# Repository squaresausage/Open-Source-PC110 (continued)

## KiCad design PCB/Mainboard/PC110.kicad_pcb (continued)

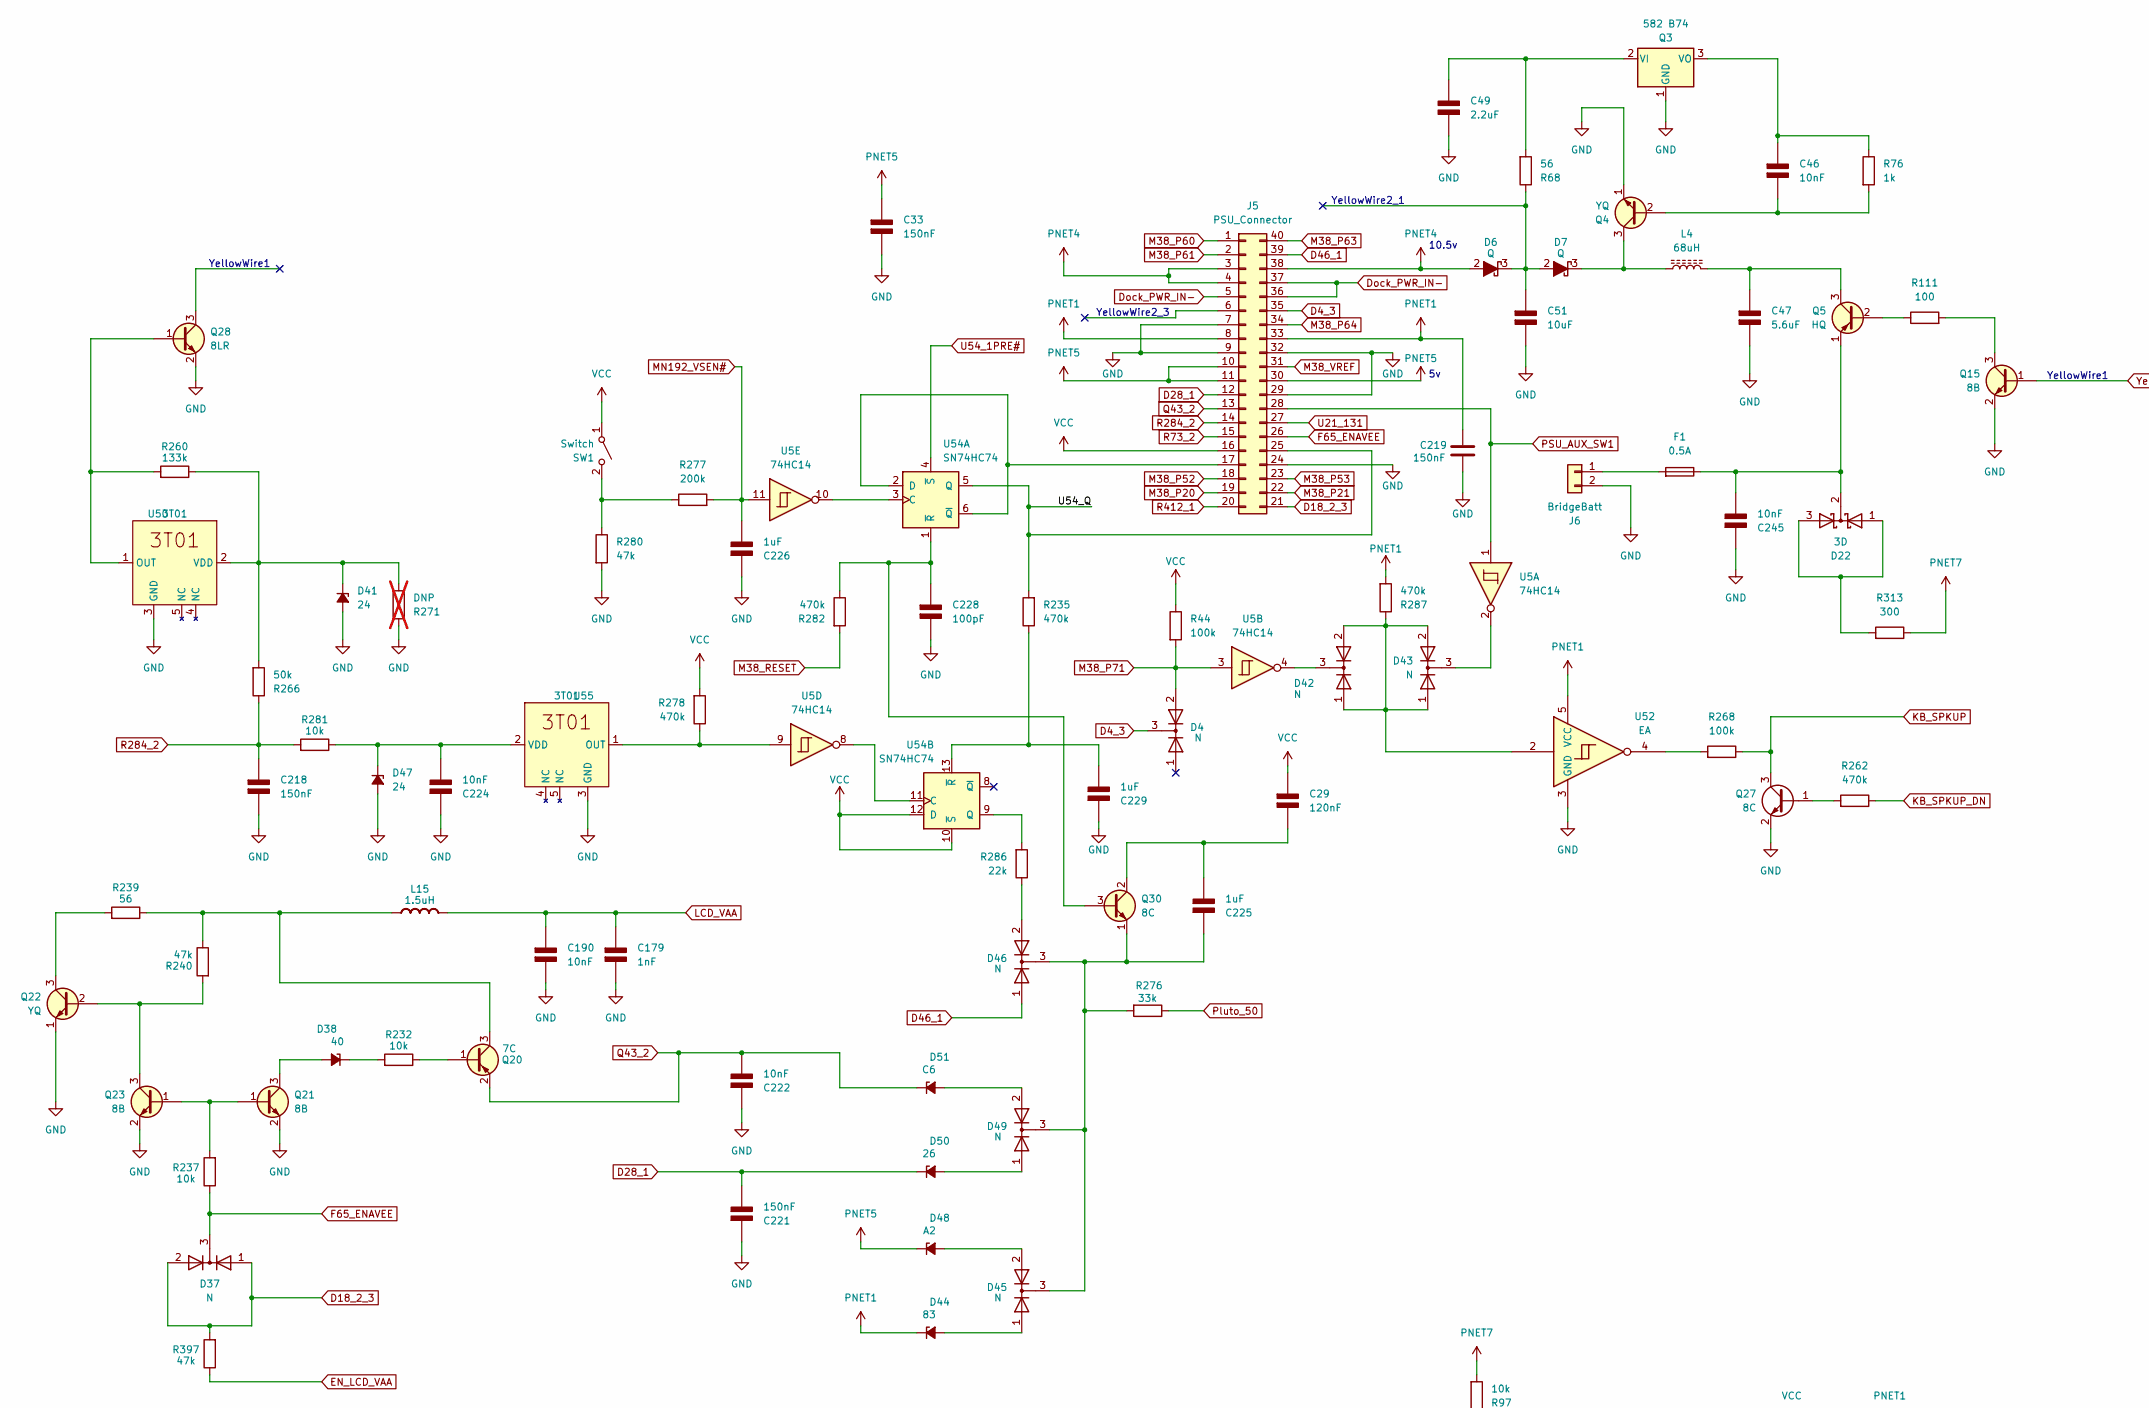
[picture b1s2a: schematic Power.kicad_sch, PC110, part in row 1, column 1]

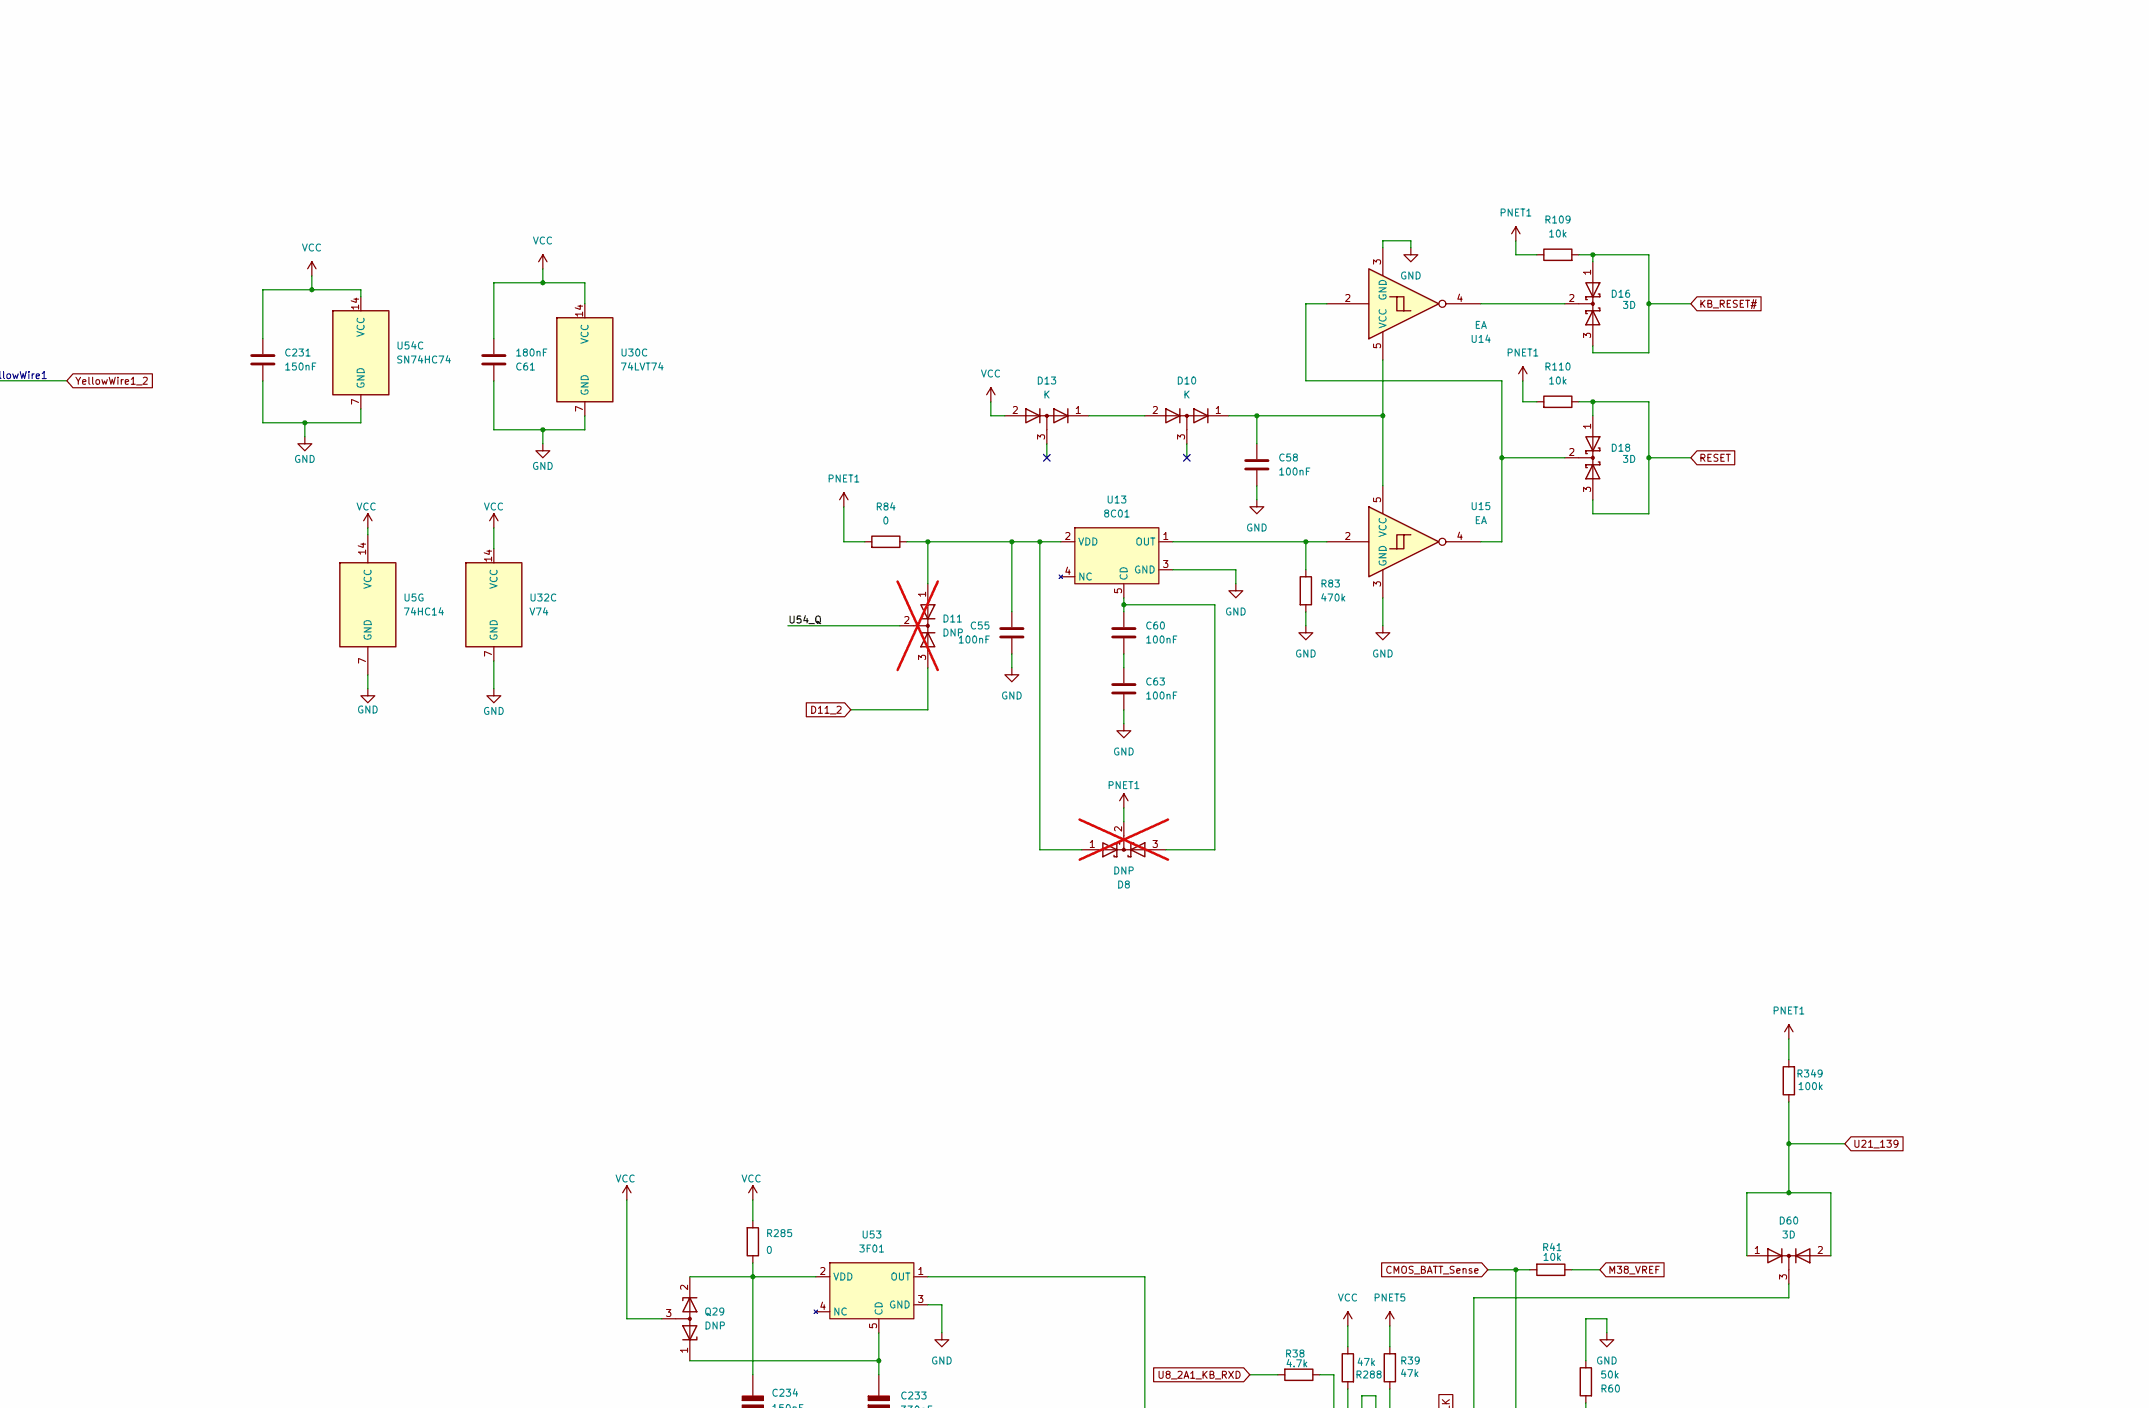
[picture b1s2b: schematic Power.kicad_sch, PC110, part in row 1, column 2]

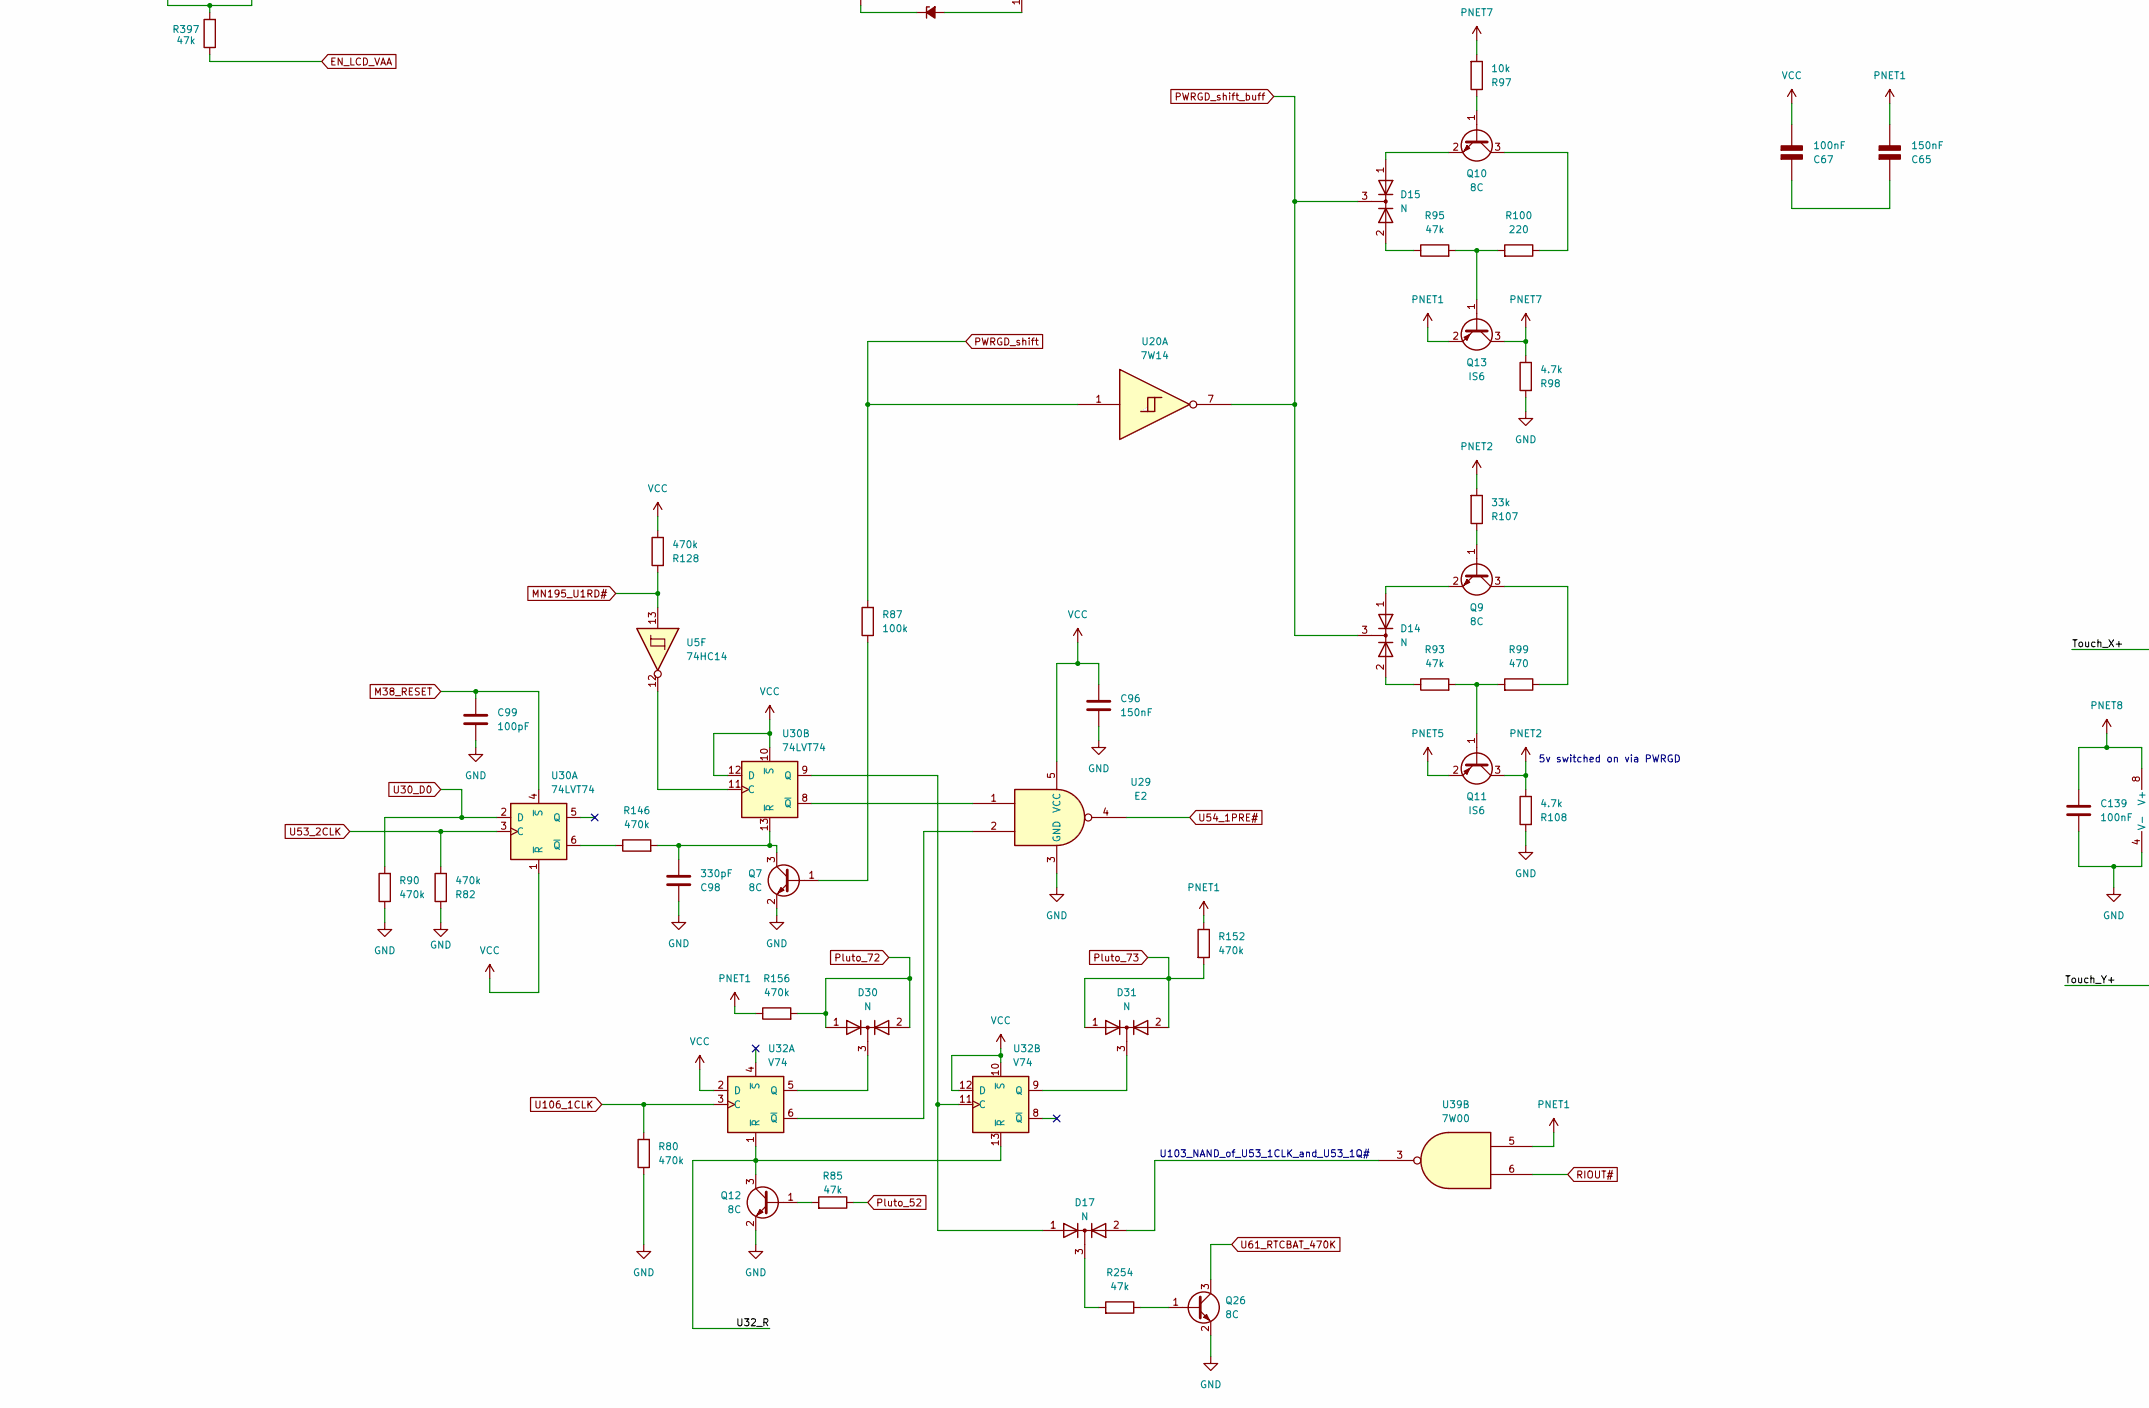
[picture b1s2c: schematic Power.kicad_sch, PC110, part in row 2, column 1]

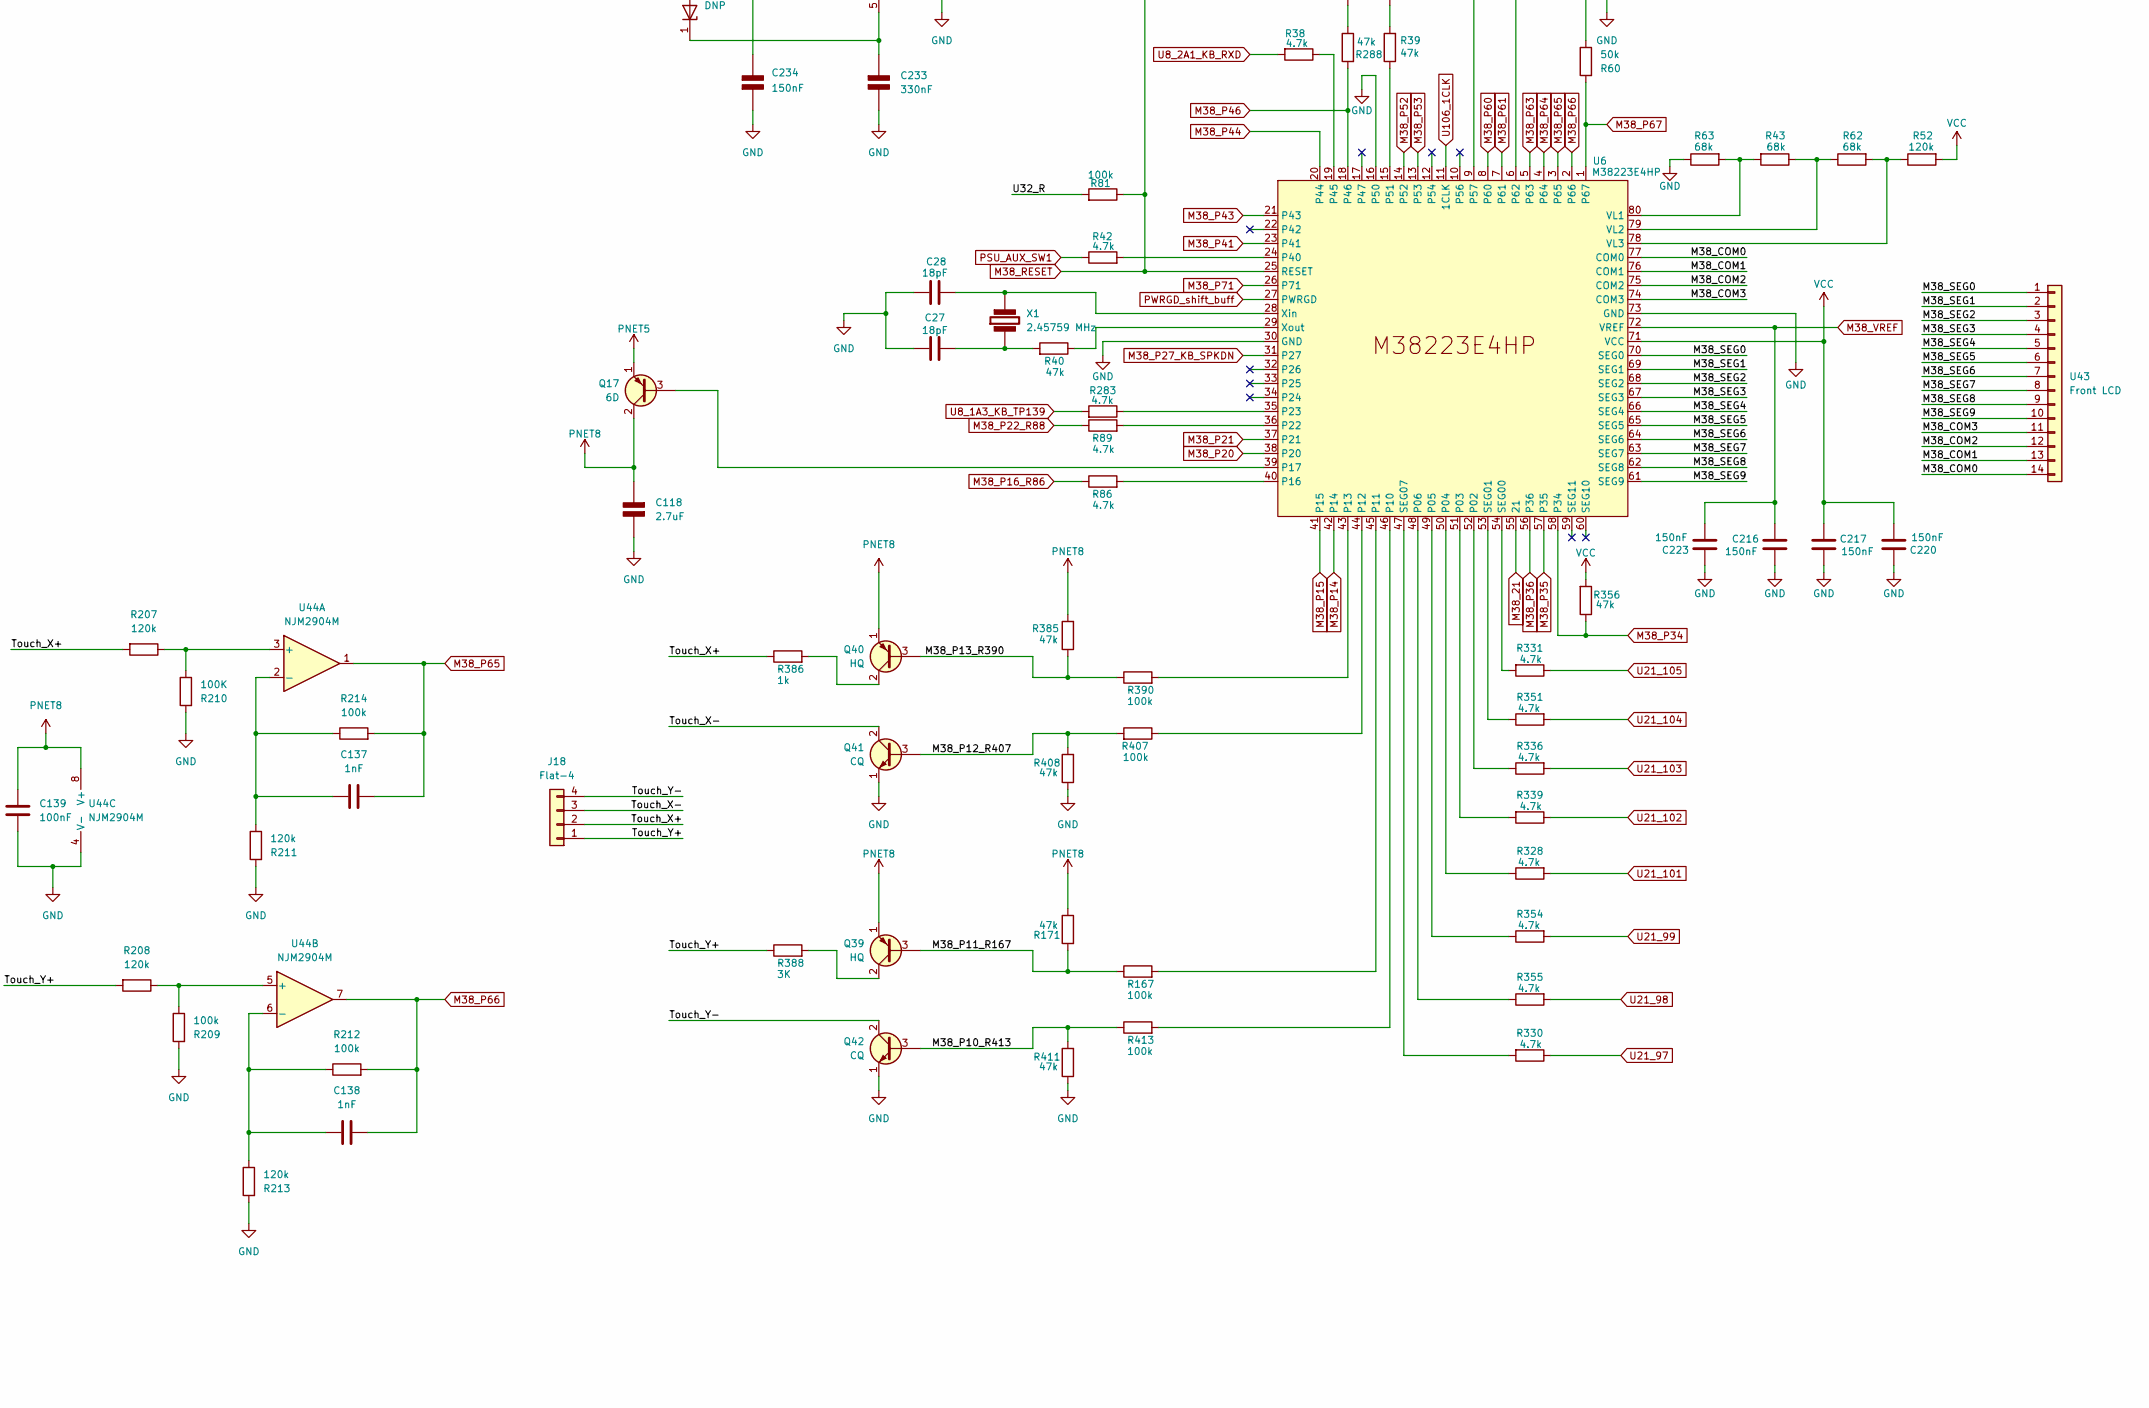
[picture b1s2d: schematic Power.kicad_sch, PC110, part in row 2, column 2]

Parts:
C27, C28: 18pF; C_0402_1005Metric
C29: 120nF; C_0402_1005Metric
C33, C65, C96, C216, C217, C219, C220, C223, C231, C234: 150nF; C_0402_1005Metric
C46, C190, C222, C224, C245: 10nF; C_0603_1608Metric
C47: 5.6uF; C_1206_3216Metric
C49: 2.2uF; C_0805_2012Metric
C51: 10uF; C_1206_3216Metric
C55, C58, C67, C139: 100nF; C_0402_1005Metric
C60, C63: 100nF; C_0603_1608Metric
C61: 180nF; C_0402_1005Metric
C98: 330pF; C_0402_1005Metric
C99, C228: 100pF; C_0402_1005Metric
C118: 2.7uF; C_0805_2012Metric
C137, C138, C179: 1nF; C_0402_1005Metric
C218, C221: 150nF; C_0603_1608Metric
C225, C226, C229: 1uF; C_0603_1608Metric
C233: 330nF; C_0603_1608Metric
D4, D14, D15, D17, D30, D31, D37, D42, D43, D45, D46, D49: N; SOT-416L
D6, D7: Q; 3D
D8, D11: DNP; 3D; not fitted
D10, D13: K; SOT-416L
D16, D18, D22: 3D
D38: 40; D_0603_1608Metric
D41, D47: 24; D_0603_1608Metric
D44: 83; D_0603_1608Metric
D48: A2; D_0603_1608Metric
D50: 26; D_0603_1608Metric
D51: C6; D_0603_1608Metric
D60: 3D; SOT-23
F1: 0.5A; Fuse_1206_3216Metric
J5: PSU_Connector
J6: BridgeBatt
J18: Flat-4
L4: 68uH; L_1210_3225Metric
L15: 1.5uH; L_0603_1608Metric
Q3: 582 B74; SOT-89-3
Q4, Q22: YQ; SOT-416L
Q5: HQ; SOT-416L
Q7, Q10, Q12, Q26, Q27, Q30: 8C; SOT-416
Q9: 8C; SOT-523
Q11, Q13: IS6; SOT-23
Q15, Q21, Q23: 8B; SOT-416
Q17: 6D; 3D
Q20: 7C; TSOT-23
Q28: 8LR; SOT-416
Q29: DNP; SOT-23
Q39, Q40: HQ; TSOT-23
Q41, Q42: CQ; TSOT-23
R38, R42, R86, R89, R98, R108, R283, R328, R330, R331, R336, R339, R351, R354, R355: 4.7k; R_0402_1005Metric
R39, R40, R85, R93, R95, R171, R240, R254, R280, R288, R356, R385, R397, R408, R411: 47k; R_0402_1005Metric
R41, R97, R109, R110, R232, R237, R281: 10k; R_0402_1005Metric
R43, R62, R63: 68k; R_0402_1005Metric
R44, R81, R87, R167, R209, R212, R214, R268, R349, R390, R407, R413: 100k; R_0402_1005Metric
R52, R207, R208, R211, R213: 120k; R_0402_1005Metric
R60, R266: 50k; R_0402_1005Metric
R68: 56; R_0805_2012Metric
R76, R386: 1k; R_0402_1005Metric
R80, R82, R83, R90, R128, R146, R152, R156, R235, R262, R278, R282, R287: 470k; R_0402_1005Metric
R84, R285: 0; R_0402_1005Metric
R99: 470; R_0402_1005Metric
R100: 220; R_0402_1005Metric
R107, R276: 33k; R_0402_1005Metric
R111: 100; R_0603_1608Metric
R210: 100K; R_0402_1005Metric
R239: 56; R_0603_1608Metric
R260: 133k; R_0402_1005Metric
R271: DNP; R_0402_1005Metric; not fitted
R277: 200k; R_0402_1005Metric
R286: 22k; R_0402_1005Metric
R313: 300; R_0805_2012Metric
R388: 3K; R_0402_1005Metric
SW1: Switch
U5: 74HC14; TSSOP-14_4.4x5mm_P0.65mm
U6: M38223E4HP; QFN-80
U13: 8C01; SOT-23-5
U14, U15, U52: EA; SOT-353
U20: 7W14; sso-8
U29: E2; SOT-353
U30: 74LVT74; TSSOP-14_4.4x5mm_P0.65mm
U32: V74; TSSOP-14_4.4x5mm_P0.65mm
U39: 7W00; sso-8
U43: Front LCD; LCD
U44: NJM2904M; soic-8-small
U50: 3T01; SOT-23-5
U53: 3F01; TSOP-5_1.65x3.05mm_P0.95mm
U54: SN74HC74; TSSOP-14_4.4x5mm_P0.65mm
U55: 3T01; TSOP-5_1.65x3.05mm_P0.95mm
X1: 2.45759 MHz; XTAL-2

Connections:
/Power/M38_COM0: U6.77 (COM0), U43.14
/Power/M38_COM1: U6.76 (COM1), U43.13
/Power/M38_COM2: U6.75 (COM2), U43.12
/Power/M38_COM3: U6.74 (COM3), U43.11
/Power/M38_P10_R413: Q42.3 (B), R411.2, R413.1
/Power/M38_P11_R167: Q39.3 (B), R167.1, R171.2
/Power/M38_P12_R407: Q41.3 (B), R407.2, R408.2
/Power/M38_P13_R390: Q40.3 (B), R385.1, R390.1
/Power/M38_SEG0: U6.70 (SEG0), U43.1
/Power/M38_SEG1: U6.69 (SEG1), U43.2
/Power/M38_SEG2: U6.68 (SEG2), U43.3
/Power/M38_SEG3: U6.67 (SEG3), U43.4
/Power/M38_SEG4: U6.66 (SEG4), U43.5
/Power/M38_SEG5: U6.65 (SEG5), U43.6
/Power/M38_SEG6: U6.64 (SEG6), U43.7
/Power/M38_SEG7: U6.63 (SEG7), U43.8
/Power/M38_SEG8: U6.62 (SEG8), U43.9
/Power/M38_SEG9: U6.61 (SEG9), U43.10
/Power/Touch_X+: J18.2, R207.2, R386.1
/Power/Touch_X-: J18.3, Q41.2 (C)
/Power/Touch_Y+: J18.1, R208.2, R388.1
/Power/Touch_Y-: J18.4, Q42.2 (C)
/Power/U32_R: Q12.3 (C), R81.2, U32.1 (~R), U32.13 (~R)
/Power/U54_Q: D11.2 (K), J5.25, R235.2, U54.5 (Q)
CMOS_BATT_Sense: R41.2, U6.6 (P62); also elsewhere on the board
D4_3: D4.3, J5.35
D18_2_3: D37.1, D37.2, J5.21, R397.2
D28_1: C221.2 (-), D50.1 (K), J5.12; also elsewhere on the board
D46_1: D46.1, J5.39
Dock_PWR_IN-: J5.5, J5.36, J5.37; also elsewhere on the board
EN_LCD_VAA: R397.1; also elsewhere on the board
F65_ENAVEE: D37.3, J5.26, R237.1; also elsewhere on the board
KB_RESET#: D16.1 (A), D16.3 (A), R109.2; also elsewhere on the board
KB_SPKUP: Q27.3 (C), R268.1; also elsewhere on the board
KB_SPKUP_DN: R262.1; also elsewhere on the board
LCD_VAA: C179.1 (+), C190.1 (+), L15.1 (+); also elsewhere on the board
M38_21: U6.55 (21); also elsewhere on the board
M38_P14: U6.42 (P14); also elsewhere on the board
M38_P15: U6.41 (P15); also elsewhere on the board
M38_P16_R86: R86.1; also elsewhere on the board
M38_P20: J5.19, U6.38 (P20)
M38_P21: J5.22, U6.37 (P21)
M38_P22_R88: R89.1; also elsewhere on the board
M38_P27_KB_SPKDN: U6.31 (P27); also elsewhere on the board
M38_P34: R356.1, U6.58 (P34); also elsewhere on the board
M38_P35: U6.57 (P35); also elsewhere on the board
M38_P36: U6.56 (P36); also elsewhere on the board
M38_P41: U6.23 (P41); also elsewhere on the board
M38_P43: U6.21 (P43); also elsewhere on the board
M38_P44: U6.20 (P44); also elsewhere on the board
M38_P46: R288.2, U6.18 (P46); also elsewhere on the board
M38_P52: J5.18, U6.14 (P52)
M38_P53: J5.23, U6.13 (P53)
M38_P60: J5.1, U6.8 (P60)
M38_P61: J5.2, U6.7 (P61)
M38_P63: J5.40, U6.5 (P63)
M38_P64: J5.34, U6.4 (P64)
M38_P65: C137.2, R214.2, U6.3 (P65), U44.1
M38_P66: C138.2, R212.2, U6.2 (P66), U44.7
M38_P67: R60.2, U6.1 (P67); also elsewhere on the board
M38_P71: D4.2, R44.2, U5.3, U6.26 (P71)
M38_RESET: C99.2, R81.1, R282.2, U6.25 (RESET), U30.4 (~S), U53.1 (OUT)
M38_VREF: C216.1, C223.2, J5.31, R41.1, U6.72 (VREF)
MN192_VSEN#: C226.2 (-), R277.2, U5.11; also elsewhere on the board
MN195_U1RD#: R128.2, U5.13; also elsewhere on the board
unnamed: C46.1 (+), Q3.3 (VO), R76.1
unnamed: C46.2 (-), Q4.2 (B), R76.2
unnamed: C47.1 (+), L4.1, Q5.3 (C)
unnamed: C49.2 (-), Q3.2 (VI), R68.2
unnamed: C60.1, C63.2
unnamed: C65.1 (+), C67.1 (+)
unnamed: C224.2 (-), D47.1 (K), R281.1, U55.2 (VDD)
unnamed: C225.1 (+), D45.3, D46.3, D49.3, Q30.1 (E), R276.2
unnamed: C29.2 (-), C225.2 (-), Q30.2 (C)
unnamed: C228.1 (+), Q30.3 (B), R282.1, U54.1 (~R)
unnamed: C229.2 (-), R235.1, U54.13 (~R)
unnamed: C233.1 (+), Q29.1 (K), U53.5 (CD)
unnamed: C234.2 (-), Q29.2 (K), R285.1, U53.2 (VDD)
unnamed: C245.2 (-), D22.2 (K), F1.1, Q5.1 (E)
unnamed: D7.3 (K), L4.2, Q4.3 (C)
unnamed: D10.2 (A), D13.1 (K)
unnamed: C58.2, D10.1 (K), U14.5 (VCC), U15.5 (VCC)
unnamed: D14.2, R93.1
unnamed: D15.2, R95.1
unnamed: D16.2 (K), U14.4
unnamed: D17.2, U39.3
unnamed: D17.3, R254.2
unnamed: D18.2 (K), U14.2, U15.4
unnamed: D22.1 (A), D22.3 (A), R313.2
unnamed: D38.2 (A), Q21.3 (C)
unnamed: D38.1 (K), R232.2
unnamed: D41.1 (K), R260.1, R266.2, R271.2, U50.2 (VDD)
unnamed: D42.1, D42.2, D43.1, D43.2, R287.1, U52.2
unnamed: D42.3, U5.4
unnamed: D43.3, U5.2
unnamed: D44.2 (A), D45.1
unnamed: D46.2, R286.1
unnamed: D45.2, D48.2 (A)
unnamed: D49.1, D50.2 (A)
unnamed: D49.2, D51.2 (A)
unnamed: J5.17, U54.2 (D), U54.6 (~Q)
unnamed: F1.2, J6.1
unnamed: L15.2 (-), Q20.3 (C), R239.1, R240.1
unnamed: Q5.2 (B), R111.1
unnamed: Q7.1 (B), R87.1
unnamed: C98.1, Q7.3 (C), R146.2, U30.13 (~R)
unnamed: Q9.1 (B), R107.1
unnamed: Q9.3 (C), R99.1
unnamed: D14.1, Q9.2 (E)
unnamed: Q10.1 (B), R97.1
unnamed: Q10.3 (C), R100.1
unnamed: D15.1, Q10.2 (E)
unnamed: Q11.1 (B), R93.2, R99.2
unnamed: Q12.1 (B), R85.2
unnamed: Q13.1 (B), R95.2, R100.2
unnamed: Q15.3 (C), R111.2
unnamed: Q17.3 (B), U6.39 (P17)
unnamed: Q20.1 (B), R232.1
unnamed: Q21.1 (B), Q23.1 (B), R237.2
unnamed: Q22.2 (B), Q23.3 (C), R240.2
unnamed: Q22.3 (C), R239.2
unnamed: Q26.1 (B), R254.1
unnamed: Q27.1 (B), R262.2
unnamed: Q28.1 (B), R260.2, U50.1 (OUT)
unnamed: Q39.2 (C), R388.2
unnamed: Q40.2 (C), R386.2
unnamed: R268.2, U52.4
unnamed: R277.1, R280.1, SW1.2 (B)
unnamed: R336.1, U6.52 (P02)
unnamed: R339.2, U6.51 (P03)
unnamed: R328.1, U6.50 (P04)
unnamed: R354.1, U6.49 (P05)
unnamed: R355.1, U6.48 (P06)
unnamed: R413.2, U6.46 (P10)
unnamed: R167.2, U6.45 (P11)
unnamed: R407.1, U6.44 (P12)
unnamed: R390.2, U6.43 (P13)
unnamed: R86.2, U6.40 (P16)
unnamed: R89.2, U6.36 (P22)
unnamed: R283.1, U6.35 (P23)
unnamed: R42.2, U6.24 (P40)
unnamed: R38.1, U6.19 (P45)
unnamed: R39.1, U6.15 (P51)
unnamed: D60.3, U6.9 (P57)
unnamed: R331.2, U6.54 (SEG00)
unnamed: R351.1, U6.53 (SEG01)
unnamed: R330.2, U6.47 (SEG07)
unnamed: R43.2, R63.2, U6.80 (VL1)
unnamed: R43.1, R62.1, U6.79 (VL2)
unnamed: R52.1, R62.2, U6.78 (VL3)
unnamed: C28.1, U6.28 (Xin), X1.1 (+)
unnamed: R40.1, U6.29 (Xout)
unnamed: C60.2, D8.3 (A), U13.5 (CD)
unnamed: R83.1, U13.1 (OUT), U15.2
unnamed: C55.2, D8.1 (A), D11.1 (A), R84.1, U13.2 (VDD)
unnamed: R146.1, U30.6 (~Q)
unnamed: U5.12, U30.11 (C)
unnamed: D17.1, U30.9 (Q), U32.11 (C)
unnamed: U29.1, U30.8 (~Q)
unnamed: D30.3, U32.5 (Q)
unnamed: U29.2, U32.6 (~Q)
unnamed: D31.3, U32.9 (Q)
unnamed: R207.1, R210.1, U44.3 (+)
unnamed: C137.1, R211.1, R214.1, U44.2 (-)
unnamed: R208.1, R209.1, U44.5 (+)
unnamed: C138.1, R212.1, R213.1, U44.6 (-)
unnamed: U5.10, U54.3 (C)
unnamed: U5.8, U54.11 (C)
unnamed: R286.2, U54.9 (Q)
unnamed: R278.1, U5.9, U55.1 (OUT)
unnamed: C27.1, R40.2, X1.2 (-)
PNET1: C65.2 (-), C219.1, D8.2 (K), D44.1 (K), J5.8, J5.33, Q13.2 (E), R84.2, R109.1, R110.2, R152.1, R156.1, R287.2, R349.2, U39.5, U52.5 (VCC); also elsewhere on the board
PNET2: Q11.3 (C), R107.2, R108.1; also elsewhere on the board
PNET4: D6.2 (A), J5.3, J5.4, J5.38; also elsewhere on the board
PNET7: Q13.3 (C), R97.2, R98.1, R313.1; also elsewhere on the board
PNET8: C118.1 (+), C139.2, Q17.2 (C), Q39.1 (E), Q40.1 (E), R171.1, R385.2, U44.8 (V+)
PSU_AUX_SW1: J5.28, R42.1, U5.1
PWRGD_shift: R87.2, U20.1; also elsewhere on the board
PWRGD_shift_buff: D14.3, D15.3, U6.27 (PWRGD), U20.7; also elsewhere on the board
Pluto_50: R276.1; also elsewhere on the board
Pluto_52: R85.1; also elsewhere on the board
Pluto_72: D30.1, D30.2, R156.2; also elsewhere on the board
Pluto_73: D31.1, D31.2, R152.2; also elsewhere on the board
Q43_2: C222.2 (-), D51.1 (K), J5.13, Q20.2 (E)
R73_2: J5.15; also elsewhere on the board
R284_2: C218.1 (+), J5.14, R266.1, R281.2
R412_1: J5.20; also elsewhere on the board
RESET: D18.1 (A), D18.3 (A), R110.1; also elsewhere on the board
RIOUT#: U39.6; also elsewhere on the board
U8_1A3_KB_TP139: R283.2; also elsewhere on the board
U8_2A1_KB_RXD: R38.2; also elsewhere on the board
U21-99: R354.2; also elsewhere on the board
U21_97: R330.1; also elsewhere on the board
U21_98: R355.2; also elsewhere on the board
U21_101: R328.2; also elsewhere on the board
U21_102: R339.1; also elsewhere on the board
U21_103: R336.2; also elsewhere on the board
U21_104: R351.2; also elsewhere on the board
U21_105: R331.1; also elsewhere on the board
U21_131: J5.27; also elsewhere on the board
U21_139: D60.1, D60.2, R349.1; also elsewhere on the board
U30_D0: R90.2, U30.2 (D); also elsewhere on the board
U53_2CLK: R82.1, U30.3 (C); also elsewhere on the board
U54_1PRE#: U29.4, U54.4 (~S)
U61_RTCBAT_470K: Q26.3 (C); also elsewhere on the board
U106_1CLK: R80.2, U6.11 (1CLK), U32.3 (C)
VCC: C29.1 (+), C61.1, C67.2 (-), C96.2, C217.1, C220.2, C231.2, D13.2 (A), J5.16, Q29.3 (A), R44.1, R52.2, R128.1, R278.2, R285.2, R288.1, R356.2, SW1.1 (A), U5.14 (VCC), U6.71 (VCC), U29.5 (VCC), U30.1 (~R), U30.10 (~S), U30.12 (D), U30.14 (VCC), U32.2 (D), U32.10 (~S), U32.12 (D), U32.14 (VCC), U54.10 (~S), U54.12 (D), U54.14 (VCC); also elsewhere on the board
YellowWire1_2: Q15.1 (B); also elsewhere on the board

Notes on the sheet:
YellowWire2_3
5v switched on via PWRGD
YellowWire2_1
10.5v
YellowWire1
U103_NAND_of_U53_1CLK_and_U53_1Q#
